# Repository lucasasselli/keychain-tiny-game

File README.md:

# Keychain Tiny Game

# Features
- Beautiful state of the art 1D graphics
- One button gameplay
- Can hold keys
- No microtransactions

# The idea
I recently bought a novelty keychain: it's a handmade leather pouch designed to protect my phone screen from scratches while adding a touch of style. Unfortunately, it’s more of a hindrance than a help, making it difficult to use my keys and turning me into a bumbling character from a horror movie that can't open the door to safety. That truth is that keys are naturally scratchy, and they seem to resent being kept away from their preferred surfaces. 

This keychain isn’t just a time-wasting game for dentist appointments, it’s also a collection of 24 tiny, sharp SMD components waiting to sand down my phone screen the first time I accidentally put it in the wrong pocket.

# Gameplay
Press the button when the spinning light reaches the target. Do it again slightly faster. Repeat until it's your turn at the dentist, doctor, barber, etc...

# Hardware
The board utilizes an ATtiny25 microcontroller running at 1MHz to drive 16 LEDs via [Charlieplexing](https://en.wikipedia.org/wiki/Charlieplexing). A single button on the back of the board allows for game control. The device is powered by a single CR2032 coin cell battery.

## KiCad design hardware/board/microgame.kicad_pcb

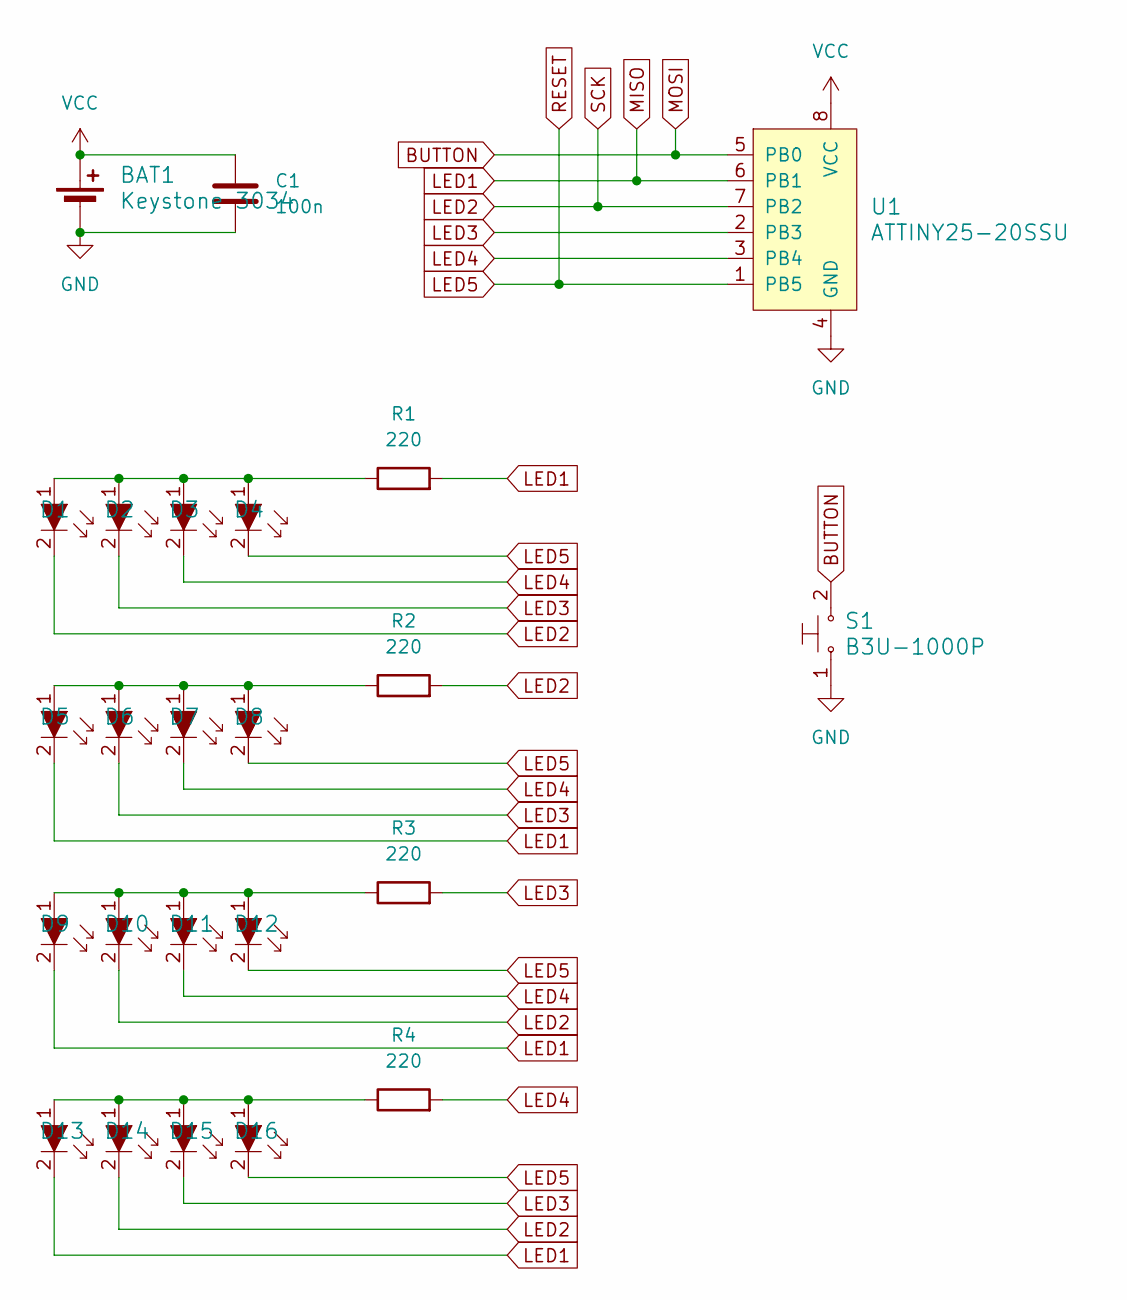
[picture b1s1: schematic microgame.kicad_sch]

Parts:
BAT1: Keystone 3034; BatteryHolder_Keystone_3034_1x20mm; MPN BS-7; Digi-Key_PN BS-7-ND
C1: 100n; C_0603_1608Metric
D1, D2, D3, D4, D5, D6, D7, D8, D9, D10, D11, D12, D13, D14, D15, D16: LH_R974-LP-1; 0805; MPN LH R974-LP-1; Digi-Key_PN 475-1415-1-ND
R1, R2, R3, R4: 220; R_0603_1608Metric
S1: B3U-1000P; Switch_Tactile_SMD_B3U-1000P; MPN B3U-1000P; Digi-Key_PN SW1020CT-ND
U1: ATTINY25-20SSU; SOIC-8_W5.3mm; MPN ATTINY85-20SU; Digi-Key_PN ATTINY85-20SU-ND

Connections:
BUTTON: S1.2, U1.5 (PB0)
GND: BAT1.2 (-), C1.1, S1.1, U1.4 (GND)
LED1: D5.2, D9.2, D13.2, R1.2, U1.6 (PB1)
LED2: D1.2, D10.2, D14.2, R2.2, U1.7 (PB2)
LED3: D2.2, D6.2, D15.2, R3.2, U1.2 (PB3)
LED4: D3.2, D7.2, D11.2, R4.2, U1.3 (PB4)
LED5: D4.2, D8.2, D12.2, D16.2, U1.1 (PB5)
unnamed: D1.1, D2.1, D3.1, D4.1, R1.1
unnamed: D5.1, D6.1, D7.1, D8.1, R2.1
unnamed: D9.1, D10.1, D11.1, D12.1, R3.1
unnamed: D13.1, D14.1, D15.1, D16.1, R4.1
VCC: BAT1.1 (+), C1.2, U1.8 (VCC)

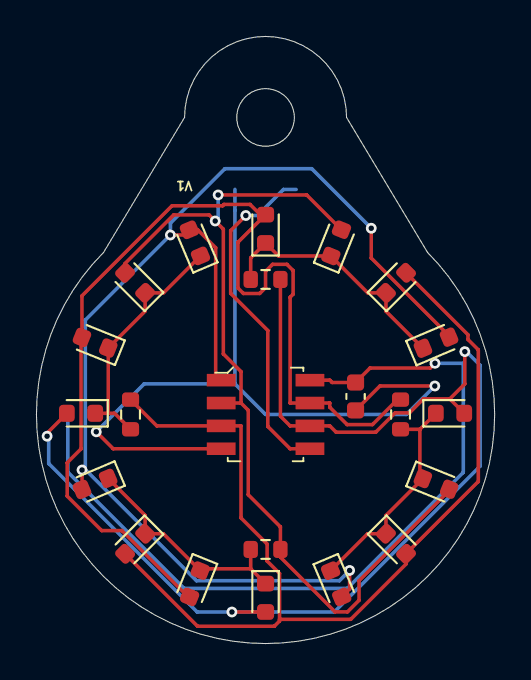
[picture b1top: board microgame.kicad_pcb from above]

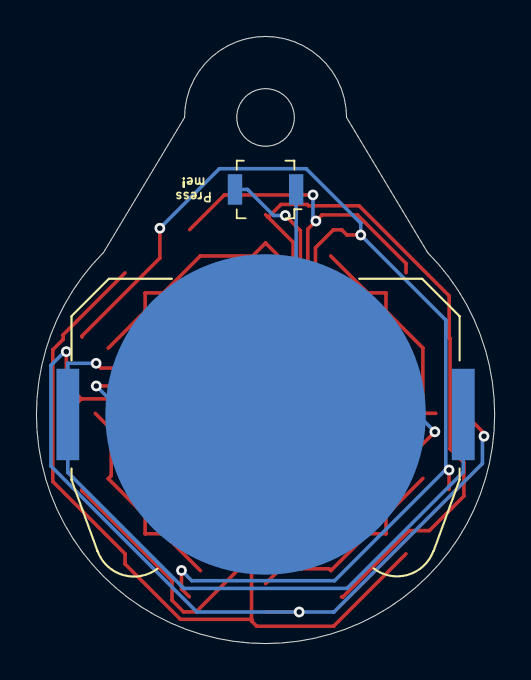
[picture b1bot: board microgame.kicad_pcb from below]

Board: 2 copper layers, 25.5 x 33.7 mm, 24 parts (2 on the bottom side), 12 nets.

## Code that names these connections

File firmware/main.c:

#include <avr/interrupt.h>
#include <avr/io.h>
#include <avr/sleep.h>
#include <stdlib.h>

#define BIT(pos) (1 << (pos))
#define GET_BIT(x, pos) ((x >> pos) & 1)
#define SET_BIT(x, pos) ((x) |= (BIT(pos)))
#define CLEAR_BIT(x, pos) ((x) &= ~(BIT(pos)))

#define LED_CNT 16

#define BTN_DEBOUNCE_NUM 10
#define BTN_PIN PB0

#define CURSOR_TIME_BASE 800
#define CURSOR_TIME_STAGE_DELTA 16
#define INIT_SPIN_TIME 100
#define INIT_SPIN_NUM 3
#define FAIL_TIME 8000
#define GAME_TIMEOUT 40000
#define GAME_MAX_STAGES 45
#define WIN_TIME 8000

const uint8_t cplex_pins[LED_CNT][2] = {
    // Group 0
    {PB1, PB2},
    {PB1, PB3},
    {PB1, PB4},
    {PB1, PB5},

    // Group 1
    {PB2, PB1},
    {PB2, PB3},
    {PB2, PB4},
    {PB2, PB5},

    // Group 2
    {PB3, PB1},
    {PB3, PB2},
    {PB3, PB4},
    {PB3, PB5},

    // Group 3
    {PB4, PB1},
    {PB4, PB2},
    {PB4, PB3},
    {PB4, PB5},
};

typedef enum {
    GAME_INIT,
    GAME_ACTIVE,
    GAME_FAIL,
    GAME_WIN
} game_state_t;

// Game
game_state_t game_state;  // Current game state
uint8_t game_init_cnt;    // Number of loops furing init animation
uint8_t game_stage;       // Stage
uint8_t game_target;      // Target light position
uint8_t game_cursor;      // Cursor light position
uint8_t game_dir;         // Cursor direction

uint16_t idle_time = 0;
uint16_t timer_ovf_cnt = 0;

// Button
uint8_t btn_pressed_cnt;  // De-bounce counter
uint8_t btn_state;        // Button filtered state
uint8_t btn_old_state;    // Button old state (for edge detection)

void game_target_rand() {
    game_target = rand() % LED_CNT;  // Pick a new target
#ifdef SKIP_RST_PIN
    if ((game_target % 4) == 3) game_target_rand();
#endif
}

void game_init() {
    // Configure timer
    TCCR0A = 0x00;  // Normal mode
    TCCR0B = 0x00;
    TCCR0B |= (1 << CS00);  // No prescaling
    TCNT0 = 0;

    // Configure button pin as input with pull-up resistor
    DDRB &= ~(1 << BTN_PIN);
    SET_BIT(PORTB, BTN_PIN);

    // Setup game
    game_state = GAME_INIT;
    game_init_cnt = 0;
    game_cursor = 0;
    game_dir = 0;
    idle_time = 0;
    timer_ovf_cnt = 0;

    game_target_rand();  // Pick a random target
}

void led_off() {
    PORTB &= (1 << BTN_PIN);
    DDRB &= (1 << BTN_PIN);
}

void led_set_index(uint8_t i) {
    uint8_t val = PORTB & (1 << BTN_PIN);
    uint8_t dir = DDRB & (1 << BTN_PIN);

    SET_BIT(val, cplex_pins[i][0]);
    SET_BIT(dir, cplex_pins[i][0]);
    SET_BIT(dir, cplex_pins[i][1]);

    PORTB = val;
    DDRB = dir;
}

void sleep() {
    // Configure IO
    GIMSK |= _BV(PCIE);    // Enable Pin Change Interrupts
    PCMSK |= _BV(PCINT0);  // Use PB0 as interrupt pin

    DDRB = 0;  // All pin on High-Z

    set_sleep_mode(SLEEP_MODE_PWR_DOWN);

    sleep_enable();  // Sets the Sleep Enable bit in the MCUCR Register (SE BIT)
    sei();           // Enable interrupts
    sleep_cpu();     // sleep

    cli();            // Disable interrupts
    sleep_disable();  // Clear SE bit
}

void cursor_next() {
    if (game_cursor == LED_CNT) {
        game_cursor = 0;
    } else {
        game_cursor++;
    }

#ifdef SKIP_RST_PIN
    if ((game_cursor % 4) == 3) cursor_next();
#endif
}

void cursor_prev() {
    if (game_cursor == 0) {
        game_cursor = LED_CNT - 1;
    } else {
        game_cursor--;
    }
#ifdef SKIP_RST_PIN
    if ((game_cursor % 4) == 3) cursor_prev();
#endif
}

void game_do_init() {
    if (timer_ovf_cnt > INIT_SPIN_TIME) {
        cursor_next();

        if (game_cursor == game_target) {
            game_init_cnt++;
            if (game_init_cnt > INIT_SPIN_NUM) {
                // Init animation complete! Start the game...
                game_state = GAME_ACTIVE;
                game_stage = 0;  // Start from stage 0
            }
        }

        // Reset IRQ counter
        timer_ovf_cnt = 0;
    }

    // Program the LED
    led_set_index(game_cursor);
}

void game_do_active() {
    idle_time++;

    if (timer_ovf_cnt > (CURSOR_TIME_BASE - ((uint16_t)game_stage) * CURSOR_TIME_STAGE_DELTA)) {
        // Move lights clockwise
        if (game_dir) {
            cursor_next();
        } else {
            cursor_prev();
        }

        // Reset IRQ counter
        timer_ovf_cnt = 0;
    }

    // De-bounce button
    if (!GET_BIT(PINB, BTN_PIN)) {
        if (btn_pressed_cnt < BTN_DEBOUNCE_NUM) {
            btn_pressed_cnt++;
        } else {
            btn_state = 1;
        }
    } else {
        if (btn_pressed_cnt > 0) {
            btn_pressed_cnt--;
        } else {
            btn_state = 0;
        }
    }

    if (btn_state == 1 && btn_old_state == 0) {
        // Positive edge
        if (game_cursor == game_target) {
            // Target hit! Move to next stage...
            game_dir ^= 1;       // Change direction
            game_target_rand();  // Pick a random target

            game_stage++;  // Increase the stage
            if (game_stage > GAME_MAX_STAGES) {
                // Game over! Show the win animation...
                game_state = GAME_WIN;
            }
        } else {
            // Target missed! Set state to fail...
            game_state = GAME_FAIL;
        }
        idle_time = 0;
    }

    btn_old_state = btn_state;

    // Tooggle between target and cursor, but keep cursor active more!
    if ((timer_ovf_cnt & 7) == 1) {
        led_set_index(game_target);
    } else {
        led_set_index(game_cursor);
    }

    // Check for idle time and put device to sleep if necessary
    if (idle_time > GAME_TIMEOUT) {
        sleep();
        game_init();
    }
}

void game_do_fail() {
    if (timer_ovf_cnt > FAIL_TIME) {
        // Win animation complete! Start again
        game_init();  // Reset game
    }

    // Blink last cursor LED
    if (GET_BIT(timer_ovf_cnt, 7)) {
        led_set_index(game_cursor);
    } else {
        led_off();
    }
}

void game_do_win() {
    if (timer_ovf_cnt > WIN_TIME) {
        // Win animation complete! Start again
        game_init();  // Reset game
    }

    // Blink all LEDs
    if (GET_BIT(timer_ovf_cnt, 7)) {
        cursor_next();
        led_set_index(game_cursor);
    } else {
        led_off();
    }
}

int main() {
    game_init();

    while (1) {
        // Time game execution with timer overflow
        if (GET_BIT(TIFR, TOV0)) {
            SET_BIT(TIFR, TOV0);  // Clear timer overflow (W1TC)

            // Game logic
            switch (game_state) {
                case GAME_INIT:
                    game_do_init();
                    break;

                case GAME_ACTIVE:
                    game_do_active();
                    break;

                case GAME_FAIL:
                    game_do_fail();
                    break;

                case GAME_WIN:
                    game_do_win();
                    break;
            }

            timer_ovf_cnt++;
        }
    }
}

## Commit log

2024-07-20 Moved the button to the back.
2024-07-27 Updated design to have a sane pin mapping. Added initial simulator program and firmware.
2024-09-07 Updated BOM
2024-09-07 Last commit before giving up on SimAVR
2024-09-08 Initial firmware implementation
2024-09-08 Improved game mechanics
2024-09-08 Added win animation
2024-09-09 Renamed hardware project. Code cleanup. Added images.
2024-10-05 Added Test and Release mode for build
2024-10-05 Added comment for Release mode
